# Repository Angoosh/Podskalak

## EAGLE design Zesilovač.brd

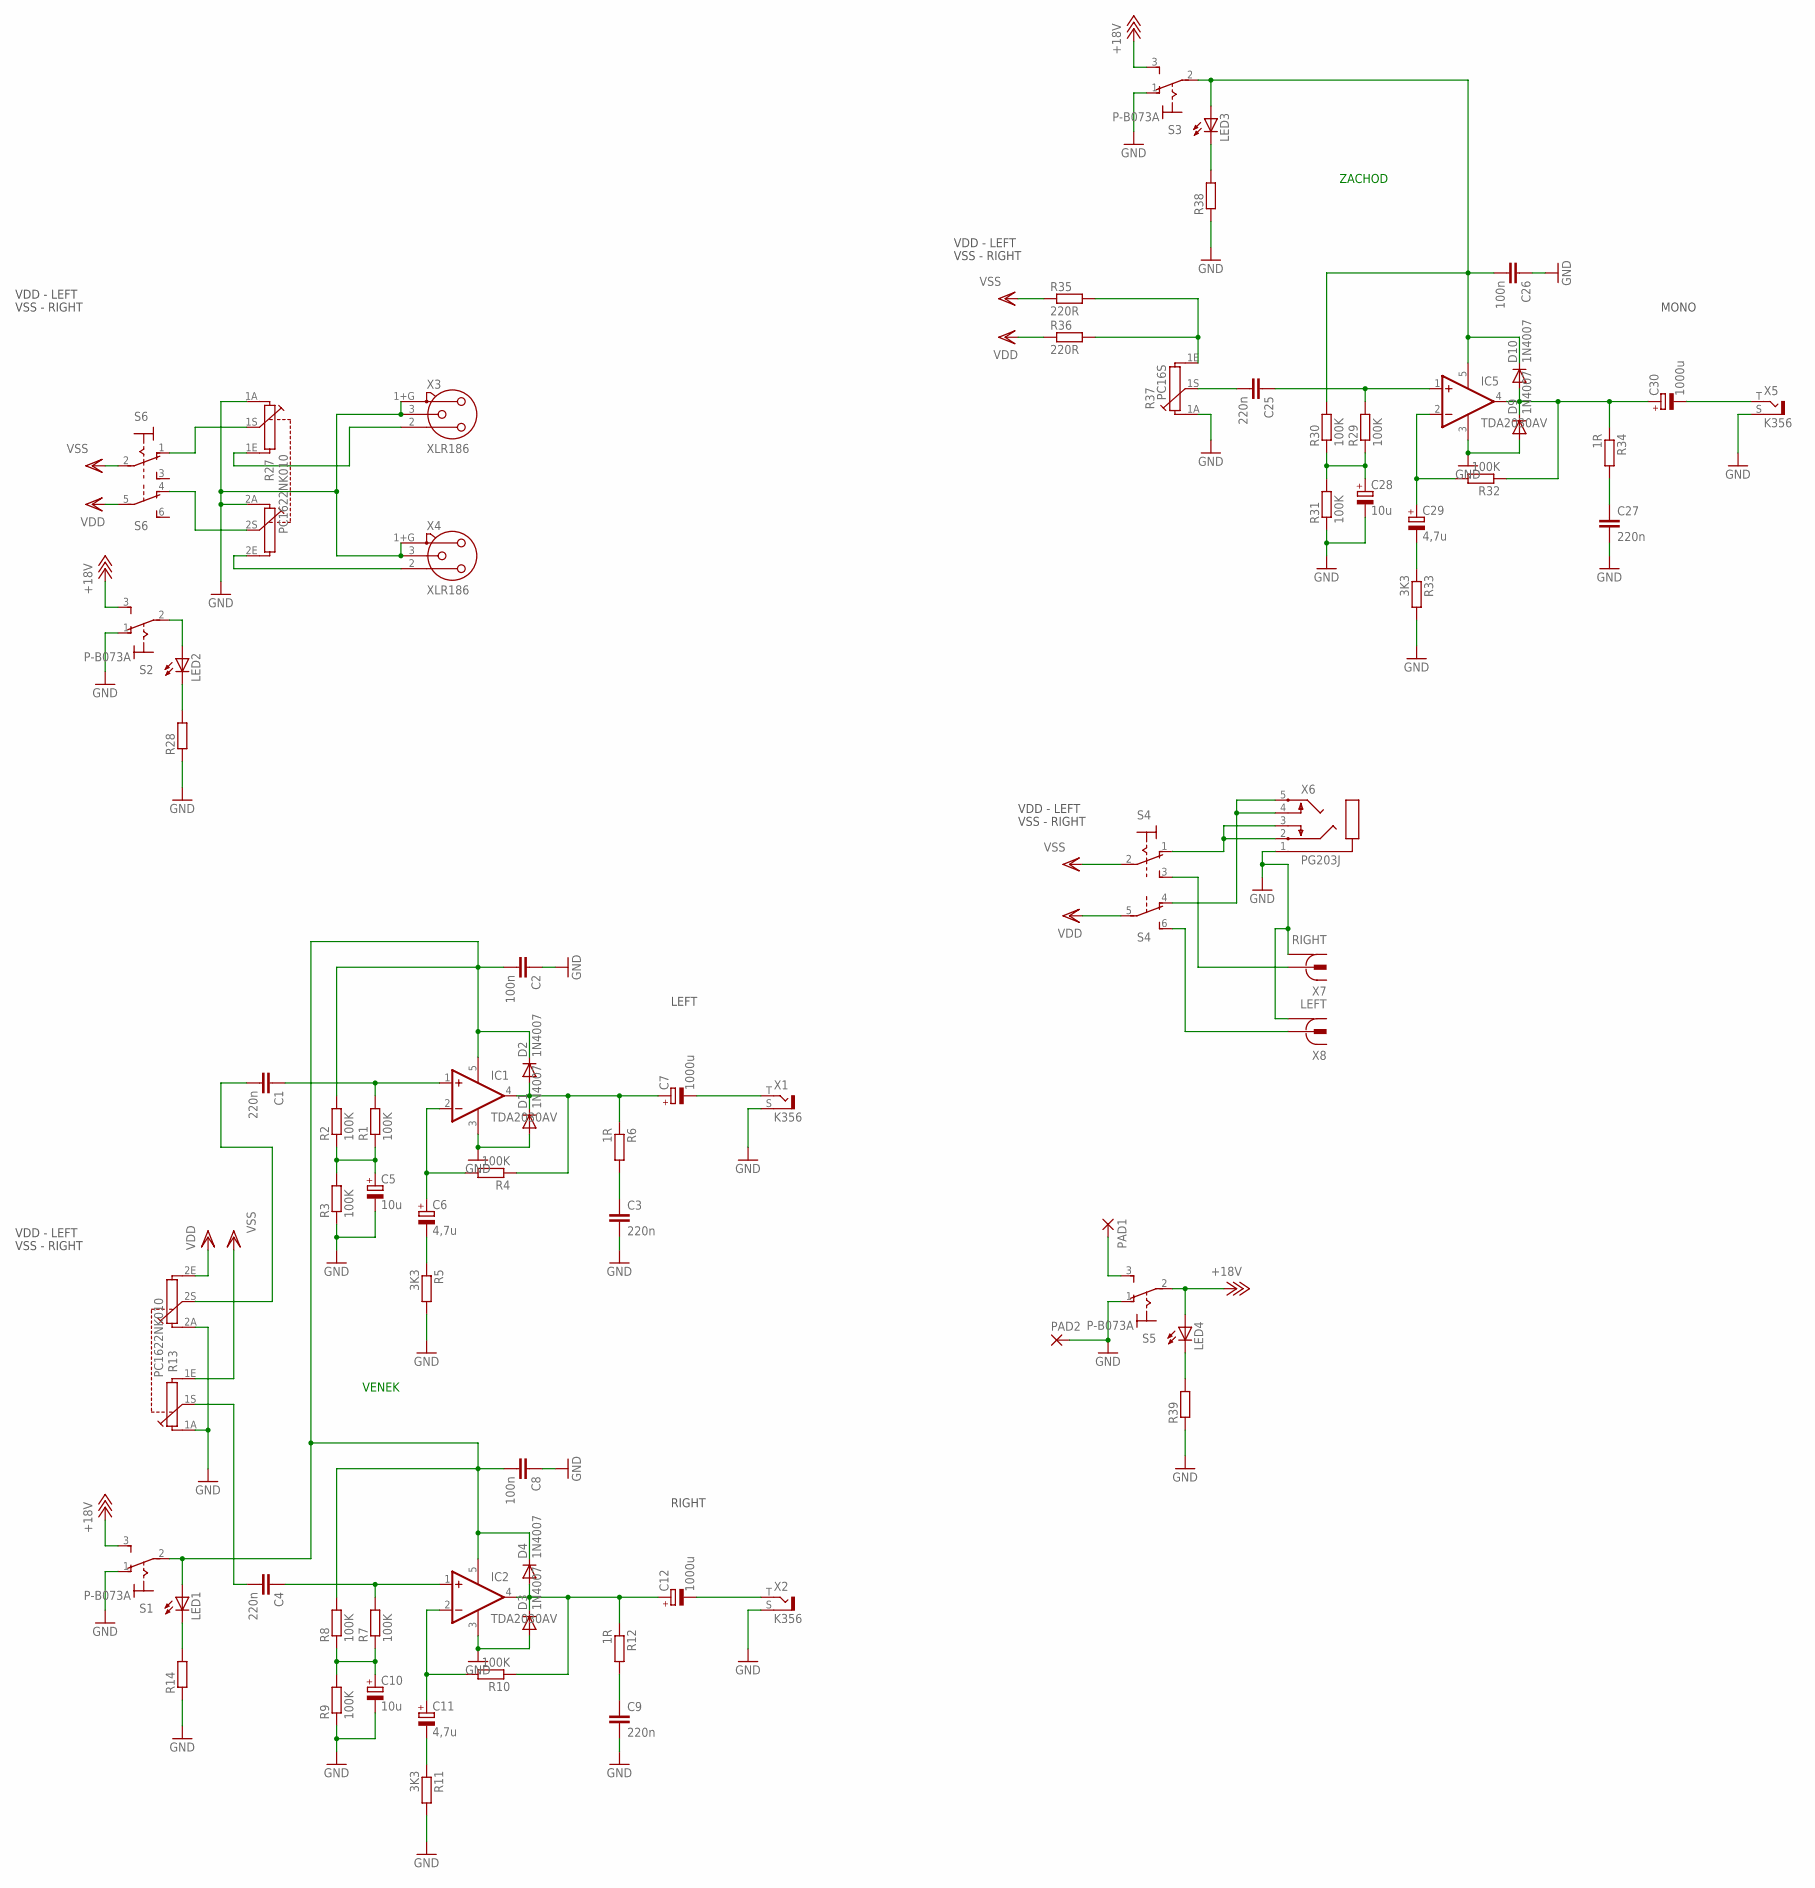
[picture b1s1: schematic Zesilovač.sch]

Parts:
C1, C3, C4, C9, C25, C27: 220n; C5B2.5
C2, C8, C26: 100n; C5B2.5
C5, C10, C28: 10u; E2-4
C6, C11, C29: 4,7u; E2,5-6
C7, C12, C30: 1000u; E3,5-8
D1, D2, D3, D4, D9, D10: 1N4007; DO41-10
IC1, IC2, IC5: TDA2030AV; CB360
LED1, LED2, LED3, LED4: LED_ELD260; LED_LD260
PAD1, PAD2: 3,81/1,4
R1, R2, R3, R4, R7, R8, R9, R10, R29, R30, R31, R32: 100K; 0204/7
R5, R11, R33: 3K3; 0204/7
R6, R12, R34: 1R; 0207/10
R13, R27: PC1622NK010; PC16D
R14, R28, R38, R39: R0204/7; 0204/7
R35, R36: 220R; 0204/7
R37: PC16S
S1, S2, S3, S5: P-B073A; 320-916
S4, S6: 320-938
X1, X2, X5: K356; RC-5231
X3, X4: XLR186; NC3FAV1-0
X6: PG203J
X7: RIGHT; 736880-49
X8: LEFT; 736880-49

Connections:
+18V: LED4.A, S1.3 (S), S2.3 (S), S3.3 (S), S5.2
GND: C2.1, C3.2, C5.-, C8.1, C9.2, C10.-, C26.1, C27.2, C28.-, D1.A, D3.A, D9.A, IC1.3 (GND), IC2.3 (GND), IC5.3 (GND), PAD2.1, R3.1, R5.2, R9.1, R11.2, R13.1A, R13.2A, R14.1, R27.1A, R27.2A, R28.1, R31.1, R33.2, R37.1A, R38.1, R39.1, S1.1 (O), S2.1 (O), S3.1 (O), S5.1 (O), X1.S, X2.S, X3.1+G (1), X3.3, X4.1+G (1), X4.3, X5.S, X6.1, X7.1, X7.1@1 (1), X7.1@2 (1), X8.1, X8.1@1 (1), X8.1@2 (1)
unnamed: C1.1, IC1.1 (+IN), R1.2
unnamed: C7.+, D1.C, D2.A, IC1.4 (OUT), R4.1, R6.1
unnamed: C5.+, R1.1, R2.1, R3.2
unnamed: C4.1, IC2.1 (+IN), R7.2
unnamed: C6.-, R5.1
unnamed: C6.+, IC1.2 (-IN), R4.2
unnamed: C3.1, R6.2
unnamed: C10.+, R7.1, R8.1, R9.2
unnamed: C11.-, R11.1
unnamed: C11.+, IC2.2 (-IN), R10.2
unnamed: C12.+, D3.C, D4.A, IC2.4 (OUT), R10.1, R12.1
unnamed: C9.1, R12.2
unnamed: C1.2, R13.2S
unnamed: C4.2, R13.1S
unnamed: R27.1S, S6.1 (O)
unnamed: C25.2, R37.1S
unnamed: R27.2S, S6.4 (O)
unnamed: LED3.K (C), R38.2
unnamed: C7.-, X1.T
unnamed: C12.-, X2.T
unnamed: LED1.K (C), R14.2
unnamed: R27.1E, X3.2
unnamed: R27.2E, X4.2
unnamed: LED2.K (C), R28.2
unnamed: C25.1, IC5.1 (+IN), R29.2
unnamed: C28.+, R29.1, R30.1, R31.2
unnamed: C29.-, R33.1
unnamed: C29.+, IC5.2 (-IN), R32.2
unnamed: C30.+, D9.C, D10.A, IC5.4 (OUT), R32.1, R34.1
unnamed: C27.1, R34.2
unnamed: R35.2, R36.2, R37.1E
unnamed: S4.1 (O), X6.2, X6.3
unnamed: C30.-, X5.T
unnamed: PAD1.1, S5.3 (S)
unnamed: S4.4 (O), X6.4, X6.5
unnamed: S4.3 (S), X7.2
unnamed: S4.6 (S), X8.2
unnamed: LED4.K (C), R39.2
unnamed: LED2.A, S2.2
VCC1: C2.2, C8.2, D2.C, D4.C, IC1.5 (V+), IC2.5 (V+), LED1.A, R2.2, R8.2, S1.2
VCC3: C26.2, D10.C, IC5.5 (V+), LED3.A, R30.2, S3.2
VDD: R13.2E, R36.1, S4.5, S6.5
VSS: R13.1E, R35.1, S4.2, S6.2

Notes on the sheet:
VDD - LEFT
VSS - RIGHT
LEFT
RIGHT
MONO
ZACHOD
VENEK

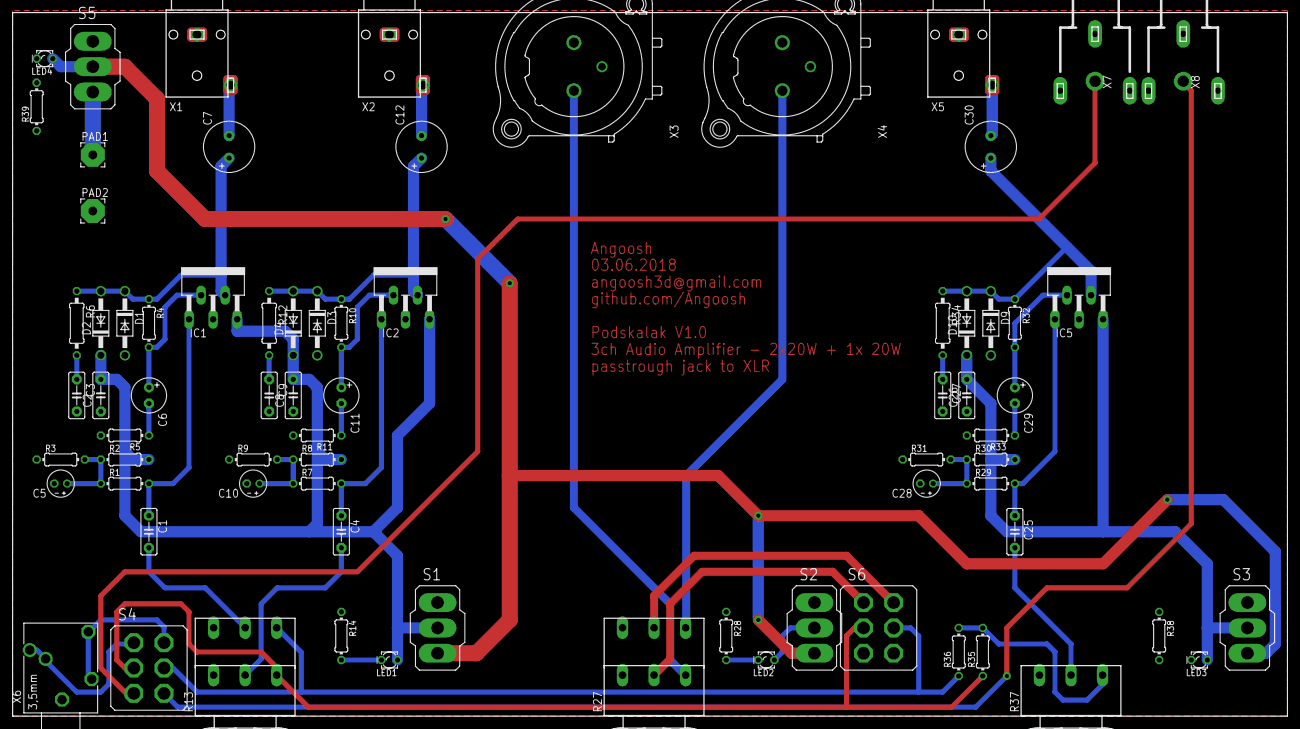
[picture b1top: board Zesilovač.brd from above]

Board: 2 copper layers, 201.9 x 111.4 mm, 74 parts (0 on the bottom side), 45 nets.

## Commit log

2018-06-16 Added things
